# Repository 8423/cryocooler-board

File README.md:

# Cryocooler Board

A 4-layer power and control board for a **Ricor K508N** cryocooler. It does two jobs, both controlled over I²C:

1. **Supplies the cryocooler's power.** A TI **TPS55288** buck-boost converter steps the 24 V rail down to an adjustable **12–20 V**.
2. **Sets the cryocooler's target temperature.** An Analog Devices **AD5258** digital potentiometer acts as the cryocooler's set-point resistor, around 170 K.

Designed in KiCad 8 by Rodrigo Spinola e Castro.

---

## Status

| Version | Tag | State |
|---|---|---|
| V1 | `v1` | First fabricated board |
| V2 | `v2` | Fabricated, faulty |
| V3 | `v3` | Fabricated. I²C and digipot work; the converter output oscillates and efficiency is very low (see [Lessons from V3](#lessons-from-v3)) |
| V4 | – | Redesign addressing V3's problems: bulk output capacitor, current limit, thermal vias. Not built |
| **V4.1** | `v4.1` | **Ordered from JLCPCB on 13 Oct 2026.** A test build to confirm the control loop is stable before space-rated parts are chosen. See [Changes in V4.1](#changes-in-v41) |

Each built version is tagged. Browse any of them with the branch/tag selector on GitHub, or compare two, e.g. `…/compare/v3...main`.

---

## Requirements

| # | Requirement |
|---|---|
| 1 | Step the 24 V rail down to a set value between **12 V and 20 V**. Expected load: up to ~2 A while cooling down, ~0.5 A at the set point. The cryocooler's maximum input power is 20 W. |
| 1a | The output must never exceed 24 V. |
| 1b | After a reset of I²C or of the 24 V supply, the output returns to **12 V**. |
| 1c | Switching noise must not interfere with the CCD electronics, so the switching frequency stays **above 500 kHz**. |
| 2 | Set the cryocooler's target temperature (around 170 K) through a variable resistor. |
| 3 | Control both the output voltage and the temperature set point over **I²C**. |
| 4 | After a reset of I²C or of power, the temperature set point returns to 170 K. |

---

## How it works

```mermaid
flowchart LR
    J1["J1<br/>24 V in"] --> U3["U3<br/>4 A fuse"] --> U1["U1 TPS55288<br/>buck-boost<br/>Q1, Q2, L1 10 µH"] --> R3["R3<br/>10 mΩ sense"] --> J2["J2<br/>12–20 V out"]
    J3["J3<br/>I²C in"] -- "0x74" --> U1
    J3 -- "0x18" --> U2["U2 AD5258<br/>1 kΩ rheostat"] --> J4["J4<br/>cryocooler<br/>set point"]
    U1 -. "VCC (5 V LDO)" .-> U2
```

- **Power path:** 24 V enters on J1 and passes through the 4 A fuse U3. The TPS55288 drives external MOSFETs Q1 and Q2 on the input side and uses inductor L1. The output passes through the 10 mΩ sense resistor R3 to J2.
- **Control:** both chips sit on one I²C bus (J3). The bus is pulled up by the host computer (3.3 V), not by this board: R1 and R2 (2.2 kΩ to VCC) are kept as footprints but **not populated** in V4.1. This is a provisional choice; see the I²C item under [Open items](#open-items-after-v41).
  - TPS55288 at **0x74**: its MODE pin is tied to ground, which also selects the internal 5 V regulator and forced PWM at light load (datasheet Table 7-2).
  - AD5258 at **0x18**: both address pins are tied to ground.
- **VCC** is the TPS55288's internal 5 V supply, made from VIN. It powers the digipot (both VDD and VLOGIC), so **both chips only respond on I²C while 24 V is present**.
- **Grounds:** analog ground (AGND) and power ground (PGND) are separate copper and joined at one point by the net tie NT1.

### Reset behaviour (requirements 1b and 4)
- **TPS55288:** it has no non-volatile memory. After a power cycle its output is **off**, and this can't be changed. The host must re-send the I²C commands to enable the output and set 12 V.
- **AD5258:** it stores its wiper setting in EEPROM and restores it at power-up. Store the 170 K setting in EEPROM to meet requirement 4.

---

## Connectors

All connectors are Molex Pico-Lock.

| Ref | Function | Part | Pin 1 | Pin 2 | Pin 3 | Pin 4 |
|---|---|---|---|---|---|---|
| **J1** | 24 V input | 4-pin 5040500491 | VIN | VIN | PGND | PGND |
| **J2** | Converter output to the cryocooler | 2-pin 2053380002 | VOUT | PGND | – | – |
| **J3** | I²C | 4-pin 5040500491 | AGND | SCL | SDA | AGND |
| **J4** | Cryocooler temperature set point | 2-pin 2053380002 | CRYO_2 | CRYO_1 | – | – |

On J1, each signal uses two pins in parallel.

Test points: TP_VIN1, TP_VOUT1, TP_PGND1, TP_AGND1, TP_SCL1, TP_SDA1, plus **TP_COMP1** (error-amplifier output) and **TP_VCC1** (gate-drive supply), new in V4.1. SW1 can be probed at the uncovered via at (129.5, 87.9) mm, on the SW1 copper beside L1; see [Bring-up notes](#bring-up-notes).

**J1 and J3 are the same 4-pin part, and J2 and J4 are the same 2-pin part.** A swapped harness puts 24 V on the I²C lines, or the converter output across the digipot. Label harnesses and check every plug before applying power.

---

## Design choices

### Converter: TPS55288 ([datasheet](https://www.ti.com/product/TPS55288))

**Why this chip:**
- 2.7–36 V input covers the 24 V rail.
- 0.8–22 V output covers 12–20 V.
- 6.35 A current limit, programmable over I²C.
- 200 kHz–2.2 MHz switching, with optional frequency dithering.
- Built-in 5 V supply for the I²C devices.

**Drawbacks:**
- The 5 V supply is inefficient when made from 24 V, so it adds some heat.
- The settings don't survive a power cycle (see above).

| Function | Parts | Value | Reasoning |
|---|---|---|---|
| Switching frequency | Rfsw1 | 32.4 kΩ → **≈610 kHz** (datasheet Eq. 3) | Above the 500 kHz CCD limit even at the low end of tolerance with dithering (≈510 kHz), but as close as practical to the chip's typical 400 kHz |
| Inductor | L1 | **10 µH**, Coilcraft XAL1010-103MED (JLC C6358489) | Gives ≈1 A ripple at the worst case (12 V out from 24 V in). The chip supports 1–10 µH; TI's evaluation board uses 4.7 µH with 3.2 A ripple at 400 kHz |
| Input-voltage turn-on | R4 / R5, C10 = 100 nF | 30 kΩ / 5.1 kΩ | Turns the converter on at ≈8 V; 24 V gives ≈3.4 V on the EN pin (limit 20 V). C10 filters the EN pin |
| Frequency dithering | Cdith1, R9 | 15 nF → **≈735 Hz** modulation | Spreads switching noise over ±7 % of the frequency. R9 is an unpopulated 0 Ω across Cdith1: fit it to turn dithering off for an A/B test |
| Input fuse | U3 | 4 A, 72 V, 1206: prosemi 1206TD-4A (JLC C2838918) on the Bel C1T (0685T4000-01) footprint | Protects the 24 V bus. More than twice the expected 1–2 A, and well above the cryocooler's 20 W. Can be swapped for a jumper |
| Input capacitors | CIN1, CIN2, CIN4, CIN3 | 2 × 10 µF + 1 µF ceramic, plus 68 µF bulk | Datasheet recommends ~21 µF ceramic, plus bulk if the supply is far away; layout copied from TI's evaluation board |
| Output capacitors | C3–C6, C7, C11 | 4 × 10 µF (Samsung CL31A106KBHNNNE, 50 V X5R) + 1 µF ceramic, plus **68 µF hybrid** (Panasonic EEH-ZA1V680XP) | ≈80 µF effective at 12 V and ≈74 µF at 20 V, because the ceramics lose most of their capacitance under DC bias. The compensation is designed for this. C11 is new in V4 |
| Boot capacitors | C1, C2 | 0.1 µF | As on TI's evaluation board |
| Input-side MOSFETs | Q1, Q2 | Infineon IPZ40N04S5L4R8ATMA1, with 1 Ω gate resistors R7 and R8 | As on TI's evaluation board. The 40 A rating is far more than needed. In V4.1, R7 sits next to Q1's gate, as TI's layout guide asks |
| Loop compensation | Rc1, Cc1, Cp1 | 26.1 kΩ, 5.6 nF C0G, **100 pF** C0G | From the datasheet's Eqs. 24–26 with C11 fitted (C11 ESR ≈35 mΩ gives Cp ≈93 pF). TI's calculator gives crossover ≈11 kHz, 72° phase margin, 13.8 dB gain margin at 12 V out, and ≈13 kHz, 66°, 9.7 dB at 20 V out (plot below); calculated, not yet measured |
| Output current limit | R3, C12 | 10 mΩ, 1 W; 0.1 µF across it | Register 02h set to 30 mV gives a **3 A** limit. C12 filters the sense lines, like C13 on TI's evaluation board. The sense point at ISP includes some output copper, so the limit may trip nearer 2.7 A |
| Average inductor current limit | R6 | 41.2 kΩ → **8 A** (≈5.8 A at the low tolerance) | Well above the ≈2.75 A peak inductor current, below the inductor's saturation and the chip's switch limits. Keeps an unstable loop from damaging the board |
| I²C address | MODE pin to AGND | 0x74 | Operating mode and VCC source can then be changed over I²C |
| VCC | CVCC1, C8, C9 | 4.7 µF + 1 µF + 0.1 µF | As on TI's evaluation board (CVCC1 is the same part as its C14). CVCC1 returns to AGND, per the datasheet pin table |

*Open-loop response from TI's TPS55288 design calculator with the V4.1 values, at 24 V in, 2 A, 605 kHz. Effective ceramic output capacitance is taken from the V3 DC-bias measurement (≈12.4 µF at 12 V, ≈6.5 µF at 20 V). At 20 V the gain margin (9.7 dB) is just under TI's 10 dB guidance.*

### Temperature set point: AD5258 ([datasheet](https://www.analog.com/en/products/ad5258.html))
- **AD5258BRMZ1:** 1 kΩ full scale in 64 steps (≈16 Ω per step), I²C, and EEPROM to restore the setting at power-up.
- **Wired as a rheostat:** the wiper W is tied to terminal A, which goes to CRYO_1. The resistance the cryocooler sees is between W and B (CRYO_2), on J4.
- **Address:** both address pins are tied to ground, giving **0x18**.

---

## Lessons from V3

On V3, I²C and the digipot worked; the digipot covers its full 1 kΩ range. The converter did not:

- **The output oscillated by several volts at ~30 kHz** around the set value. At 10 V into 160 Ω, the scope below shows about 4.5 V peak-to-peak.
- **Efficiency was ≈20 %**, against an expected 90–95 %.
- **The board ran very hot** at outputs above 16 V. At lower switching frequencies it was even less stable and failed above 17 V.

**Cause:** the compensation is designed for about 100 µF of output capacitance, ceramic plus electrolytic. V3 had only about 41 µF, all ceramic, and ceramic capacitors lose much of their capacitance at higher voltages. Measuring how the output decayed after setting 12 V showed **≈20 µF at 8–12 V** and the full 41 µF only below 8 V. With so much less capacitance than planned, the control loop was unstable.

**Changes in V4:**
- Added the 68 µF bulk output capacitor C11, bringing the nominal total to ≈109 µF (≈74–80 µF effective under DC bias).
- Extended the chip's VOUT copper pour to include C11.
- Added vias on the TPS55288 PGND pad to carry heat into the ground planes.
- Set an average inductor current limit, so an unstable loop can't damage the board.

### Changes in V4.1

V4.1 is built to answer one question: is the loop stable with the bulk capacitor fitted? Changes that only matter in space (space-rated capacitors, vacuum heat path) wait until it is.

**Values and parts**
- Cp1 22 pF → **100 pF C0G**, recalculated for C11 (ESR ≈35 mΩ).
- Cc1 changed to a **C0G** part. V3's part (C1628) was X7R ±10%.
- R6 → **41.2 kΩ** (8 A average current limit).
- R5 → **5.1 kΩ**; R4 30 kΩ; Rfsw1 32.4 kΩ; Cdith1 **15 nF**.
- Q1/Q2 symbol corrected to IPZ40N04S5L4R8ATMA1, the part on the footprint and on TI's evaluation board.
- R1/R2 (I²C pull-ups) not populated; the 3.3 V host pulls the bus up.
- J2 (output) is a 2-pin Pico-Lock; JLC lists it at 6.5 A, ample for 2 A.

**Additions**
- **C12**, 0.1 µF across the current-sense resistor.
- **R9**, an unpopulated 0 Ω across Cdith1, to switch dithering off.
- Test points **TP_COMP1** and **TP_VCC1**, and an uncovered SW1 via for probing.

**Layout**
- **R7 moved next to Q1's gate** (it was 12 mm away). The gate and its return still run on separate inner-layer traces about 3.75 mm apart, not as a pair.
- Every resistor and capacitor moved to KiCad's standard IPC footprints (0603/0805/1206). Two of the old vendor 0603 land patterns had pads too far apart for the part.
- C5 and C6 connect solidly to the top PGND pour.
- Floating copper removed; DRC clean apart from silkscreen warnings.

**Schematic housekeeping**
- Every assembled part has `MF`, `MP` and `LCSC Part #` fields. The `MP` is the part the LCSC number actually places, which for several V3 parts differs from the old footprint names.
- ERC fixes: PWR_FLAGs on VIN, PGND and AGND; pin types corrected on the custom symbols (U1 ISP → input, VCC → power output; connectors and fuse → passive; AD5258 pins typed).
- Title block and silkscreen set to V4.1.

---

## PCB

**4 layers, 1.6 mm thick, 58 × 49 mm,** with four M3 mounting holes. The stackup follows TI's evaluation board.

| Layer | Use |
|---|---|
| Top (F.Cu) | Components; copper pour mostly PGND, plus VOUT |
| In1 | PGND plane |
| In2 | Power: VCC, AGND, VIN |
| Bottom (B.Cu) | PGND plane |

| Top | In1: PGND |
|---|---|
|  |  |
| **In2: power** | **Bottom: PGND** |
|  |  |

These images show V4.1 as ordered: each copper layer with the front silkscreen on top.

---

## Repository layout

```
cryocooler-board/
├── cryocooler-board.kicad_pro / .kicad_sch / .kicad_pcb   KiCad 8 project
├── sym-lib-table, fp-lib-table                            point at lib/ (project-relative)
├── lib/
│   ├── Cryocooler.kicad_sym     custom symbols
│   ├── Cryocooler.pretty/       custom footprints
│   └── Cryocooler.3dshapes/     3D models (STEP)
├── production/                  JLCPCB files: Gerbers zip, BOM, pick-and-place
├── docs/                        switching-converter design primer, README images
└── scripts/sw1_duty_analysis.py analyse SW1 duty cycle and efficiency from scope CSVs
```

**Opening it:** clone or download, then open `cryocooler-board.kicad_pro` in **KiCad 8**. Every non-standard symbol, footprint and 3D model is in `lib/`, so there's nothing to install. The tags `v1`–`v3` hold the old versions, but those used symbol libraries stored outside the project, so they may open with library warnings.

**Scope analysis script:**
```
python3 scripts/sw1_duty_analysis.py scope.csv --rload 176 --vin 24
```

---

## Manufacturing

Boards are made and assembled by **JLCPCB**. The production files are generated with the KiCad [Fabrication Toolkit](https://github.com/bennymeg/JLC-Plugin-for-KiCad) into `production/`.

- Give each assembled part an `LCSC Part #` field in the schematic, so the BOM names the exact JLC part. Also fill `MF` and `MP` with the part that LCSC number places.
- Resistors and capacitors use KiCad's standard footprints (`Resistor_SMD:R_0603_1608Metric` and so on). Only parts with their own package have custom footprints in `lib/`.
- The toolkit settings are in `fabrication-toolkit-options.json`: exclude DNP parts, refill zones, apply JLC rotation corrections.
- **Vias are deliberately left uncovered** so they can be used as probe points. Leave via covering as in the files when ordering.
- **Check rotations in JLC's placement view.** The toolkit only corrects standard footprints. In the V4.1 preview, U2, Q1 and Q2 (custom footprints) appeared rotated and had to be fixed by hand. To make it automatic, add a `JLCPCB Rotation Offset` field to those symbols.
- **Confirm every BOM line in JLC's tool.** In V4.1 the 10 µF ceramics, the hybrids and the 1 µF ceramics came back as "Unconfirmed" with quantity 0 until confirmed.
- 4 layers, 1.6 mm. Six vias use 0.15 mm drills (as on V3).
- The exact files sent for each order are attached to that version's GitHub Release.

---

## Bring-up notes

- **Power up from a current-limited supply (about 0.3 A at first), ramping the voltage up.** There is no reverse-polarity or surge protection. A hot-plug onto a live 24 V supply is estimated to overshoot to about 32 V with 1 m of leads, under the 35 V and 40 V ratings but not by much.
- **Check every plug before applying power** (J1/J3 and J2/J4 are look-alikes).
- **SW1:** probe the uncovered via at (129.5, 87.9) mm. The vias around it are **VIN**, not ground: never put a probe ground on them. Use a short ground lead to a PGND point. The via labelled "SW1" on the silkscreen is on the gate-return trace and also shows gate-drive spikes.
- **COMP (TP_COMP1):** use a 10× probe. A 1× probe (~100 pF) roughly doubles Cp1.
- **I²C ground is AGND.** If the I²C adapter's ground and the bench supply's negative are both earthed, part of the return current flows through AGND and NT1. Float the supply or use an isolated adapter.
- **Do not connect J4 to the K508N until its set-point input is known.** The AD5258 allows ±5 mA continuous through its terminals, which must stay between GND and VDD. At low codes its resistance is ≈75 Ω, so a set-point node above ≈0.4 V could overload it. Clamp the minimum code in firmware.

---

## Open items after V4.1

Carried to the test board and the flight design:

- [ ] **AD5258 / K508N set point:** measure the voltage and source impedance of the cryocooler's set-point input before connecting J4 (see [Bring-up notes](#bring-up-notes)).
- [ ] **High-side gate drive:** route DR1H and its SW1 return as a pair, and Kelvin-connect the return at Q1's source (TI layout guide §2.3).
- [ ] **Input switching loop:** add PGND vias at Q2's source and at the input capacitors' ground pads, and connect those pads solidly.
- [ ] **Current-sense routing:** take ISP from R3's pad as a pair with ISN, and put C12 at the IC.
- [ ] **CVCC1 ground:** AGND (datasheet pin table, current design) or PGND (TI layout guide §2.3). Try both on the test board.
- [ ] **Heat path for vacuum:** thermal vias on U1's PGND and VOUT pads, and 2 oz copper.
- [ ] **Mounting holes:** PGND copper reaches within 0.25 mm of the holes, under the screw heads. Decide whether PGND may touch the structure.
- [ ] **CIN3 and C11** are 35 V parts on a 24 V rail; confirm the bus maximum and its transients (TI's evaluation board uses 50 V on the input).
- [ ] **Connectors:** use different connectors or pin counts for J1/J3 and J2/J4, and relabel J4 (silkscreen says "Cryo out") as the set point.
- [ ] **JLC rotations:** add `JLCPCB Rotation Offset` to U2, Q1 and Q2.
- [ ] Remove the now-unused vendor passive footprints from `lib/Cryocooler.pretty/`, and update the silkscreen note "Local I2C Power, 2.2 Kohm" (R1/R2 are not populated).
- [ ] Space-rated capacitors (EEE-INST-002 derating), after the loop is shown stable.
- [ ] **I²C interface with a 3.3 V host (provisional: R1/R2 DNP).** The host drives the bus at 3.3 V with its own pull-ups. With R1/R2 populated, the 2.2 kΩ pull-ups to VCC (5.2 V) push the host's pins above its supply, so for now R1/R2 are not populated. A separate test setup confirmed both chips work this way. This matches TI's evaluation board, where the 2.2 kΩ pull-ups to VCC are optional (jumpers J5/J6) and the 3.3 V USB2ANY adapter supplies its own. Two problems remain before this is final:
  - **AD5258 input-high threshold.** Its logic supply (VLOGIC, pin 6) is tied to VCC, so it needs SCL/SDA high ≥ 0.7 × 5.2 V = **3.64 V**. A 3.3 V bus is 0.34 V short of the guaranteed level; it works in testing, but with no specified margin across temperature or parts. The TPS55288 needs only 1.2 V and is within spec. TI's evaluation board has no AD5258, so it doesn't cover this.
  - **Bus powered while 24 V is off.** VCC is then 0 V, so the host's pull-ups hold SCL/SDA above the TPS55288's VCC + 0.3 V rating and push current through the AD5258's clamp diodes into VCC (limited by the host's pull-ups; well under 1 mA).
  - **Options:** (a) keep R1/R2 DNP and accept the AD5258 margin, verifying the digipot in TVAC; (b) feed VLOGIC from a small on-board 3.3 V LDO, which brings the threshold to 2.31 V without changing J3; (c) add a level translator (PCA9306 type) with R1/R2 back as 5 V-side pull-ups, which also isolates the bus when 24 V is off but needs the host's 3.3 V on J3. Whichever is chosen, the host should keep the bus idle until 24 V is present.

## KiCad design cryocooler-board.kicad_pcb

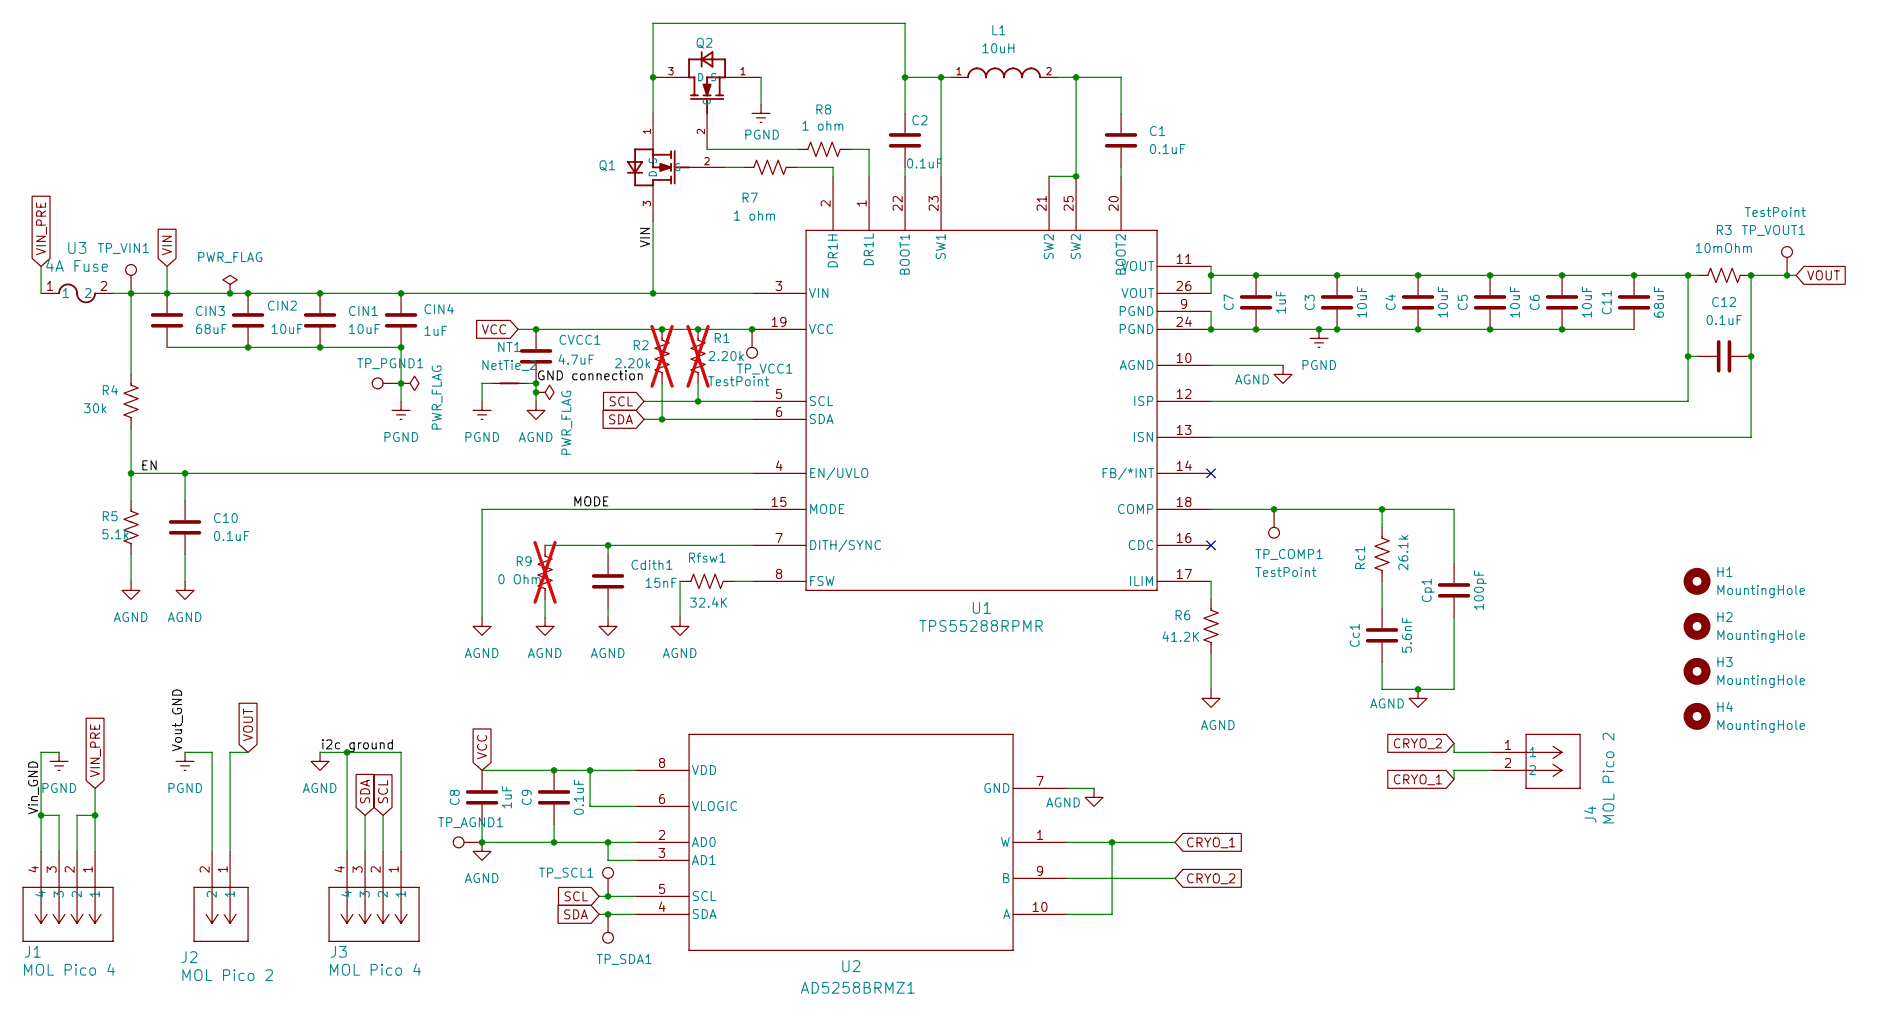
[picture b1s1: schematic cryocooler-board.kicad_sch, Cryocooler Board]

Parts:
C1, C2, C9, C10: 0.1uF; C_0805_2012Metric; LCSC Part # C85866
C3, C4, C5, C6: 10uF; C_1206_3216Metric; LCSC Part # C13585
C7, C8: 1uF; C_0603_1608Metric; LCSC Part # C49326360
C11: 68uF; EEH-ZA1V680XP; LCSC Part # C242137
C12: 0.1uF; C_0603_1608Metric; LCSC Part # C189228
CIN1, CIN2: 10uF; C_1206_3216Metric; LCSC Part # C13585
CIN3: 68uF; EEH-ZA1V680XP; LCSC Part # C242137
CIN4: 1uF; C_0603_1608Metric; LCSC Part # C49326360
CVCC1: 4.7uF; C_0603_1608Metric; LCSC Part # C437574
Cc1: 5.6nF; C_0603_1608Metric; LCSC Part # C440183
Cdith1: 15nF; C_0603_1608Metric; LCSC Part # C2180652
Cp1: 100pF; C_0603_1608Metric; LCSC Part # C71664
H1, H2, H3, H4: MountingHole; M3_3_4mm_hole
J1, J3: MOL Pico 4; MOLEX_4_pin; LCSC Part # C177235
J2, J4: MOL Pico 2; MOLEX_2_pin; LCSC Part # C17575002
L1: 10uH; XAL1010; LCSC Part # C6358489
NT1: NetTie_2; NetTie-2_SMD_Pad0.3mm
Q1, Q2: IPZ40N04S5L4R8ATMA1; LCSC Part # C6969335
R1, R2: 2.20k; R_1206_3216Metric; LCSC Part # C6538126; not fitted
R3: 10mOhm; R_1206_3216Metric; LCSC Part # C5629523
R4: 30k; R_0805_2012Metric; LCSC Part # C844838
R5: 5.1k; R_0805_2012Metric; LCSC Part # C844854
R6: 41.2K; R_1206_3216Metric; LCSC Part # C3017228
R7, R8: 1 ohm; R_0805_2012Metric; LCSC Part # C2078379
R9: 0 Ohm; R_0603_1608Metric; LCSC Part # C21189; not fitted
Rc1: 26.1k; R_0603_1608Metric; LCSC Part # C844150
Rfsw1: 32.4K; R_0603_1608Metric; LCSC Part # C844154
TP_AGND1: TestPoint; TestPoint_THTPad_D1.5mm_Drill0.7mm
TP_COMP1: TestPoint; TestPoint_THTPad_D1.5mm_Drill0.7mm
TP_PGND1: TestPoint; TestPoint_THTPad_D1.5mm_Drill0.7mm
TP_SCL1: TestPoint; TestPoint_THTPad_D1.5mm_Drill0.7mm
TP_SDA1: TestPoint; TestPoint_THTPad_D1.5mm_Drill0.7mm
TP_VCC1: TestPoint; TestPoint_THTPad_D1.5mm_Drill0.7mm
TP_VIN1: TestPoint; TestPoint_THTPad_D1.5mm_Drill0.7mm
TP_VOUT1: TestPoint; TestPoint_THTPad_D1.5mm_Drill0.7mm
U1: TPS55288RPMR; TPS55288; LCSC Part # C2864583
U2: AD5258BRMZ1; AD5258BRMZ1_IC; LCSC Part # C649444
U3: 4A Fuse; 0685T4000-01; LCSC Part # C2838918

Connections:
/EN: C10.1, R4.2, R5.1, U1.4 (EN/UVLO)
AGND: C8.2, C9.2, C10.2, CVCC1.1, Cc1.2, Cdith1.1, Cp1.2, J3.1, J3.4, NT1.2, R5.2, R6.2, R9.2, Rfsw1.1, TP_AGND1.1, U1.10 (AGND), U1.15 (MODE), U2.2 (AD0), U2.3 (AD1), U2.7 (GND)
CRYO_1: J4.2, U2.1 (W), U2.10 (A)
CRYO_2: J4.1, U2.9 (B)
unnamed: C1.1, L1.2, U1.21 (SW2), U1.25 (SW2)
unnamed: Cc1.1, Rc1.1
unnamed: Q1.2 (G), R7.1
unnamed: C2.1, L1.1, Q1.1 (S), Q2.3 (D), U1.23 (SW1)
unnamed: Q2.2 (G), R8.1
unnamed: C2.2, U1.22 (BOOT1)
unnamed: C1.2, U1.20 (BOOT2)
unnamed: Cp1.1, Rc1.2, TP_COMP1.1, U1.18 (COMP)
unnamed: Cdith1.2, R9.1, U1.7 (DITH/SYNC)
unnamed: R7.2, U1.2 (DR1H)
unnamed: R8.2, U1.1 (DR1L)
unnamed: Rfsw1.2, U1.8 (FSW)
unnamed: R6.1, U1.17 (ILIM)
unnamed: C3.1, C4.1, C5.1, C6.1, C7.1, C11.1, C12.1, R3.1, U1.11 (VOUT), U1.12 (ISP), U1.26 (VOUT)
SCL: J3.2, R1.2, TP_SCL1.1, U1.5 (SCL), U2.5 (SCL)
SDA: J3.3, R2.2, TP_SDA1.1, U1.6 (SDA), U2.4 (SDA)
VCC: C8.1, C9.1, CVCC1.2, R1.1, R2.1, TP_VCC1.1, U1.19 (VCC), U2.6 (VLOGIC), U2.8 (VDD)
VIN_PRE: J1.1, J1.2, U3.1
VOUT: C12.2, J2.1, R3.2, TP_VOUT1.1, U1.13 (ISN)

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
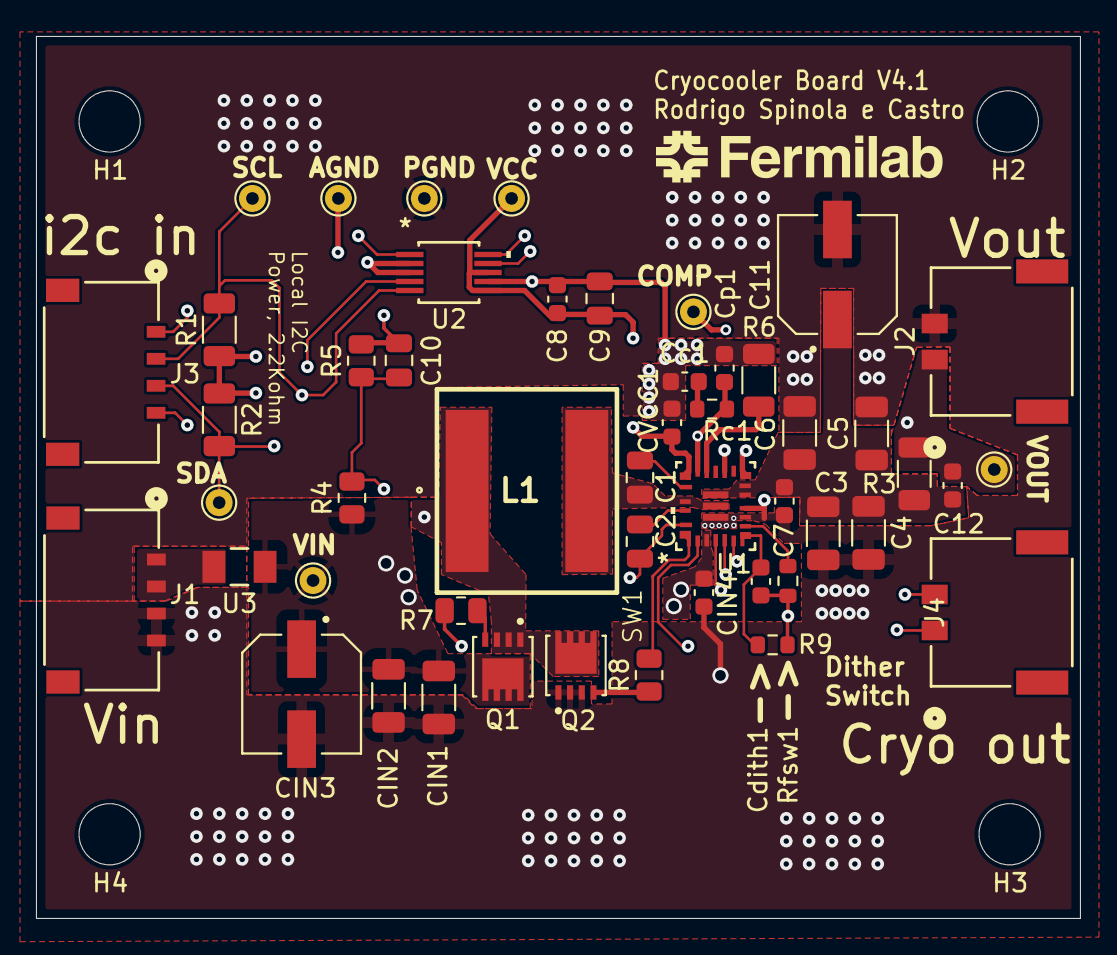
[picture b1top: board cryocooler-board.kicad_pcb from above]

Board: 4 copper layers, 58.0 x 49.0 mm, 54 parts (0 on the bottom side), 25 nets.

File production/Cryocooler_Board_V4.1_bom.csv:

Designator,Footprint,Quantity,Value,LCSC Part #
"C1, C10, C2, C9",0805,4,0.1uF,C85866
"C11, CIN3",EEH-ZA1V680XP,2,68uF,C242137
C12,0603,1,0.1uF,C189228
"C3, C4, C5, C6, CIN1, CIN2",1206,6,10uF,C13585
"C7, C8, CIN4",0603,3,1uF,C49326360
CC1,0603,1,5.6nF,C440183
CDITH1,0603,1,15nF,C2180652
CP1,0603,1,100pF,C71664
CVCC1,0603,1,4.7uF,C437574
"J1, J3",MOLEX_4_pin,2,MOL Pico 4,C177235
"J2, J4",MOLEX_2_pin,2,MOL Pico 2,C17575002
L1,XAL1010,1,10uH,C6358489
"Q1, Q2",IPZ40N04S5L4R8ATMA1,2,IPZ40N04S5L4R8ATMA1,C6969335
R3,1206,1,10mOhm,C5629523
R4,0805,1,30k,C844838
R5,0805,1,5.1k,C844854
R6,1206,1,41.2K,C3017228
"R7, R8",0805,2,1 ohm,C2078379
RC1,0603,1,26.1k,C844150
RFSW1,0603,1,32.4K,C844154
U1,TPS55288,1,TPS55288RPMR,C2864583
U2,AD5258BRMZ1_IC,1,AD5258BRMZ1,C649444
U3,0685T4000-01,1,4A Fuse,C2838918
